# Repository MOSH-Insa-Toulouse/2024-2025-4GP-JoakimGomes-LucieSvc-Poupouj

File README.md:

<!DOCTYPE html>
<html lang="fr">
<head>
  <meta charset="UTF-8">
</head>

<body>

# 2024-2025-4GP-JoakimGomes-LucieSvc-Poupouj
## Développement d'un capteur low-tech à base de Graphite : de la conception au test

### Sommaire
<hr/>
<ul>
<li> <a href="#Introduction">Introduction </a></li>
<li> <a href="#Livrables">Livrables </a></li>
<li> <a href="#Matériel à disposition">Matériel à disposition </a></li>
<li> <a href="#Simulation électronique sur LTSpice">Simulation électronique sur LTSpice </a></li>
<li> <a href="#Design du PCB avec KiCad">Design du PCB avec KiCad </a></li>
<li> <a href="#Réalisation du Shield">Réalisation du Shield </a></li>
<li> <a href="#Développement du code Arduino">Développement du code Arduino </a></li>
<li> <a href="#Développement de l'application mobile APK avec MIT App Inventor">Développement de l'application mobile APK avec MIT App Inventor </a></li>
<li> <a href="#Banc de test">Banc de test </a></li>
<li> <a href="#Datasheet">Datasheet </a></li>
<li> <a href="#Conclusion">Conclusion </a></li>
<li> <a href="#Contact">Contact </a></li>
</ul>

<h2 id="Introduction">Introduction</h2>

<p>L'UF "du capteur au banc de test" a pour objectif de concevoir un capteur low-tech et de pouvoir ensuite le tester afin de le comparer avec un capteur commercial. Le capteur est à base de graphite, que l'on retrouve notamment dans nos crayons à papier. Son développement est issu de l'article scientifique <i>"Pencil Drawn Strain Gauges and Chemiresistors on Paper"</i>(Cheng-Wei Lin*, Zhibo Zhao*, Jaemyung Kim & Jiaxing Huang). Concevoir ce capteur est relativement simple : on applique à l'aide d'un crayon, du graphite sur un morceau de papier. Les couches de graphite déposées sur le papier agissent comme un conducteur électrique qui, lorsqu'on déforme le papier, a une conductivité (et donc une résistance) qui varie. Cela s'explique par le fait que  le nombre de chaînes de particules de graphite connectées varie selon le type de déformation. En tension, il y a moins de chaines et ces dernières sont plus courtes. C'est le contraire en compression avec des chaines plus proches, laissant ainsi mieux passer le courant.</p>

<i>Figure 1 : Image issue de l'article "Pencil Drawn Strain Gauges and Chemiresistors on Paper" qui explique les déformations des chaines sous compression et tension</i>

<h2 id="Livrables">Livrables</h2>
<p>Les livrables de ce projet sont les suivants:</p>
<ul>
<li>Un schield PCB connecté à une carte Arduino UNO et contenant divers éléments:
<ul>
<li>Notre capteur de contrainte Low-tech</li>
<li>Un capteur de flexion commercial</li>
<li>Un amplificateur dont on pourra modifier le gain grâce à un potentiomètre pour le traitement du signal</li>
<li>Un écran OLED pour afficher les données du capteur</li>
<li>Un module Bluetooth permettant la communication avec un téléphone portable</li>
<li>Un encodeur rotatoire pour naviguer dans le menu de l'écran OLED</li>

</ul>
</li></br>
<li>
Le code Arduino qui permet de faire fonctionner tout le système : la communication Bluetooth, la gestion de l'écran OLED avec affichage des données, l'utilisation des deux capteurs de contrainte, la navigation dans le menu de l'écran OLED grâce à l'encodeur rotatoire, la modification du gain grâce au potentiomètre digital.
</li></br>
<li>
L'application Android developpée sur MIT App Inventor, permettant de visualiser les données directement sur son téléphone grâce à la communication Bluetooth.
</li></br>
<li>
Une datasheet pour le capteur en graphite détaillant ses performances et caractéristiques techniques.
</li></br>
</ul>

<h2 id="Matériel à disposition">Matériel à disposition</h2>
<p>Voici la liste du matériel nécessaire pour concevoir le système ci-dessus:</p>
<ul>
<li>Résistances: une résistance de 1kΩ, une résistance de 10kΩ, deux résistances de 100 kΩ, une résistance de 47kΩ pour le Flex sensor commercial et enfin un potentiomètre digital MCP41050</li>
<li>Capacités: trois capacités de 100 nF et une capacité de 1 µF</li>
<li>Un Arduino Uno</li>
<li>Un capteur graphite fait à partir d'un support papier et d'un crayon</li>
<li>Un Flex Sensor commercial</li>
<li>Un encodeur rotatoire Keyes KY-040</li>
<li>Un écran OLED 128x64</li>
<li>Un module Bluetooth HC-05</li>
<li>Un amplificateur opérationnel LTC1050</li>
</ul>

<h2 id="Simulation électronique sur LTSpice">Simulation électronique sur LTSpice</h2>
<p>Les valeurs de résistance de notre capteur graphite sont très élevées, de l'odre du MΩ. Afin de pouvoir les mesurer correctement, il est nécessaire d’amplifier le signal avant acquisition. Le courant mesuré après application d'une tension de 5V est donc très faible. Il est donc nécessaire d'amplifier le signal avant son acquisition</p>
<p>Nous avons donc simulé un montage amplificateur transimpédance sur LTspice pour l'optimiser au mieux pour notre capteur : </p>

<i>Figure 3 : Schéma de notre montage amplificateur sur LTSpice</i>
<p>Ce montage permet d'amplifier le signal du capteur à l'aide de l'amplificateur LTC1050, puis de le filtrer. Ce dernier est divisé en 3 pour limiter le bruit  :</p>
<ul>
<li> R5 et C1 : possède une fréquence de coupure de 16Hz et permet d'atténuer les bruits présents sur le signal d’entrée</li>
<li> R3 et C4 en association avec l’AOP : filtre passe-bas avec une fréquence de coupure de 1,6 Hz, qui permet de filtrer le 50 Hz du réseau électrique</li>
<li> R4 et C2 : possède une fréquence de coupure de 1,6 kHz et permet de filtrer les bruits parasites engendrés par le traitement du signal</li>
</ul>
<p>La tension mesurée, V_ADC, permet ainsi de remonter à la valeur de résistance du graphite mesurée par le capteur, R_capteur , grâce à la formule : </p>
<p>R_capteur=R1*(1+R3/R_pot)*Vcc/V_ADC-R1-R5</p>

<h2 id="Design du PCB avec KiCad">Design du PCB avec KiCad</h2>
<p>La conception du PCB s'est faite à partir du logiciel KiCad 9.0</p>
<p>Nous avons dans un premier temps reproduit le schéma électrique du système sur l'éditeur de Schématique. Il a fallu créer certains composants et récupérer d'autres dans les librairies de symboles (résistances et capacités notamment). Nous avons associé à chaque composant une empreinte et un modèle 3D. On peut alors effectuer l'ensemble des connexions entre les composants et l'Arduino via l'éditeur de Schématique.</p>

<i>Figure 4 : ensemble du fichier Schématique sous KiCad 9.0</i>

<p>Une fois le schéma électrique terminé, il faut placer les composants sur le PCB grâce à l'éditeur de PCB. L'objectif est de placer les composants judicieusement pour respecter les contraintes imposées, notamment éviter les vias, vérifier que les composants ne se superposent pas physiquement, respecter les dimensions des pistes et l'isolation.</p>

<i>Figure 5 : Disposition des composants sur l'éditeur de PCB</i>

<p>Et voici la visualisation 3D de notre PCB avec tous les composants (l'amplificateur est sous l'écran OLED).</p>

</br>
<i>Figure 6 : Visualisation 3D du PCB et composants</i>

<h2 id="Réalisation du Shield">Réalisation du Shield</h2>
<p>Une fois la conception du PCB sur KiCad terminée, nous avons pu passer à la réalisation physique de ce PCB. 
La première étape essentielle a consisté en la vérification du schéma du circuit imprimé (PCB) à l’aide du logiciel KiCad, afin de s’assurer de sa conformité avant toute fabrication. Une fois cette vérification effectuée, le masque de gravure du PCB a été généré à partir du même logiciel.
Ensuite, a fabrication a débuté par l’insolation UV d’une plaque d’époxy recouverte d’une fine couche de cuivre et d’un film photosensible. Cette exposition à la lumière permet de durcir les zones du film correspondant aux futures pistes du circuit. La plaque a ensuite été plongée dans un révélateur, ce qui a permis de dissoudre la résine restée non exposée à la lumière. La gravure des pistes a ensuite été réalisée par immersion de la plaque dans une solution de perchlorure de fer, qui attaque le cuivre non protégé par la résine insolée. Enfin, un nettoyage à l’acétone a permis de retirer les résidus de résine, révélant ainsi les pistes de cuivre définitives du circuit imprimé.
L’ensemble de ces étapes de fabrication a été réalisé par Cathy Crouzet.

Maintenant que toutes ces étapes ont été effectué, nous allons procéder au montage du capteur. Dans un premier temps, nous avons percé tous les trous afin de pouvoir souder tous les supports des composants sur la PCB. Ensuite, nous pouvons donc souder tous les supports des composants sur la PCB (cf Figure 7). Pour finir, il suffit de simplement mettre les composants sur leur support. Notre capteur est enfin prêt à être utilisé ! (cf Figure 8) </p>

</br>
<i>Figure  7: Visualisation de la face arrière de la PCB, c'est à dire les soudures.</i>

</br>
<i>Figure  8: Visualisation de la face avant de la PCB, c'est à dire les composants</i>

<h2 id="Développement du code Arduino">Développement du code Arduino</h2>
<p>Une fois la réalisation physique de notre plaque PCB effectuée, il faut à présent développer le code Arduino. Vous pouvez voir notre code sur le github dans la partie "Code Arduino" : https://github.com/MOSH-Insa-Toulouse/2024-2025-4GP-JoakimGomes-LucieSvc-Poupouj/blob/main/Code_Arduino/Capteur_graphite.ino</p>

<h2 id="Développement de l'application mobile APK avec MIT App Inventor">Développement de l'application mobile APK avec MIT App Inventor</h2>
<p>En même temps que la réalisation du code arduino, nous avons développé une application mobile APK avec MIT App Inventor. Cette application permet d'effectuer les mesures du capteur graphite, notamment obtenir un graphe  de la résistance en fonction de la tension/compression en temps réel. L'application connecte donc via le module bluetooth notre capteur avec un téléphone android.</p>

</br>
<i>Figure  9: Visualisation du code de l'application</i>

</br>
<i>Figure  10: Visualisation de l'interface de l'application</i>

<h2 id="Banc de test">Banc de test</h2>
<p>Maintenant que notre plaque PCB est réalisé virtuellement, puis physiquement, et que notre code arduino ainsi que notre application fonctionnent correctement, nous pouvons réaliser le banc de test. L'objectif est de calculer la valeur de la résistance du capteur graphite pour différentes valeurs de déformation. Pour cela nous avons utilisé un support avec des cylindres de rayons différents (1,5 cm, 2 cm, ..., 4cm). </p>
<p>Notre papier de test ayant une épaisseur e = 0,214mm nous pouvons calculer la déformation engendrée par chacun des rayons de courbure avec la formule : ϵ = e/2r</p>
<p>Nous avons donc effectué des mesures en Tension et en Compression pour des crayons de duretés différentes (2H, B, 3B, 6B) avec une valeur de potentiomètre 1 960 Ω.</p>
<p>En traçant la courbe ΔR/R0 en fonction de la déformation, la théorie nous dit que nous devons avoir une relation linéaire entre les 2. Nous avons donc tracé une droite de régression linéaire passant par 0 pour chacune des courbes et trouvons les résultats suivants :</p>

</br>
<i>Figure  11: Courbes de ΔR/R0 en fonction de la déformation en Tension</i>

</br>
<i>Figure  12: Courbes de ΔR/R0 en fonction de la déformation en Compression</i>

<p>Comme prédit par la théorie, nous pourvons observer que en Tension la résistance augmente avec la déformation, alors qu'en Compression elle diminue. De plus, plus le crayon est sec (ex : 2H) plus la pente est élevée. Nous remarquons cependant que pour le crayons 2H semble perdre en précision quand la déformation est élevée (pente de la courbe diminue). Cela peut s'expliquer car il y a très peu de chaines de particules permettant la déformation.</p>

<h2 id="Datasheet">Datasheet</h2>
<p>Le contenu de notre Datasheet se trouve avec le lien suivant : https://github.com/MOSH-Insa-Toulouse/2024-2025-4GP-JoakimGomes-LucieSvc-Poupouj/blob/main/Datasheet_Capteur_Graphite.docx</p>

<h2 id="Conclusion">Conclusion</h2>
<p>Pour conclure, ce projet capteur a été très enrichissant sur plusieurs aspect. Nous avons pu développer de nombreuses compétences, surtout sur un aspect technique. Le plus passionant au sein de ce projet étant la réalisation du projet de A à Z. En effet, nous avons commencé par la théorie, puis la pratique avec la fabrication du capteur, jusqu'au résultat final et une analyse de mesure. C'est donc un projet très complet d'un point de vue pédagogique. 

En ce qui concerne le capteur graphite réalisé, il fonctionne et est utilisable. En revanche, il manque encore grandement de précision. En effet, il n'est pas assez "stable" et "constant" lors de son utilisation. Par exemple, il ne donne pas exactement les mêmes résultats après chaque mesure réalisée de manière identique. Ceci est sûrement dû au manque de matériel de mesure précis. Effectivement, faire les mesures "à la main" n'est pas très bon d'un point de vue rigueur et scientifique. Le capteur manque parfois de graphite ou alors la flexion ou compression n'est pas exactement bien réalisée... De plus on peut voir la limite d'utilisation au crayon 2H (cf datasheet), en dessous duquel (donc crayon moins gras), il n'est plus possible d'être mesuré. Il ne peut donc pas encore être industrialisable. Cependant, nous pouvons quand même noté que le 2H fonctionne contrairement aux études menées dans "Pencil Drawn Strain Gauges and Chemiresistors on Paper"(Cheng-Wei Lin*, Zhibo Zhao*, Jaemyung Kim & Jiaxing Huang). Nous observons notamment une bonne réponse linéaire jusqu'à une déformation de 0.007 en tension.</p>

<h2 id="Contact">Contact</h2>
<p>Pour tout besoin d'informations complémentaires, veuillez nous contacter via les adresses mails INSA suivantes :</p>
<ul>
<li>Joakim GOMES CORREIA : gomescor@insa-toulouse.fr</li>
<li>Lucie SAUVIAC : sauviac@insa-toulouse.fr</li>
<li>Nicolas POUJOL : npoujol@insa-toulouse.fr</li>
</ul>

</body>
</html>

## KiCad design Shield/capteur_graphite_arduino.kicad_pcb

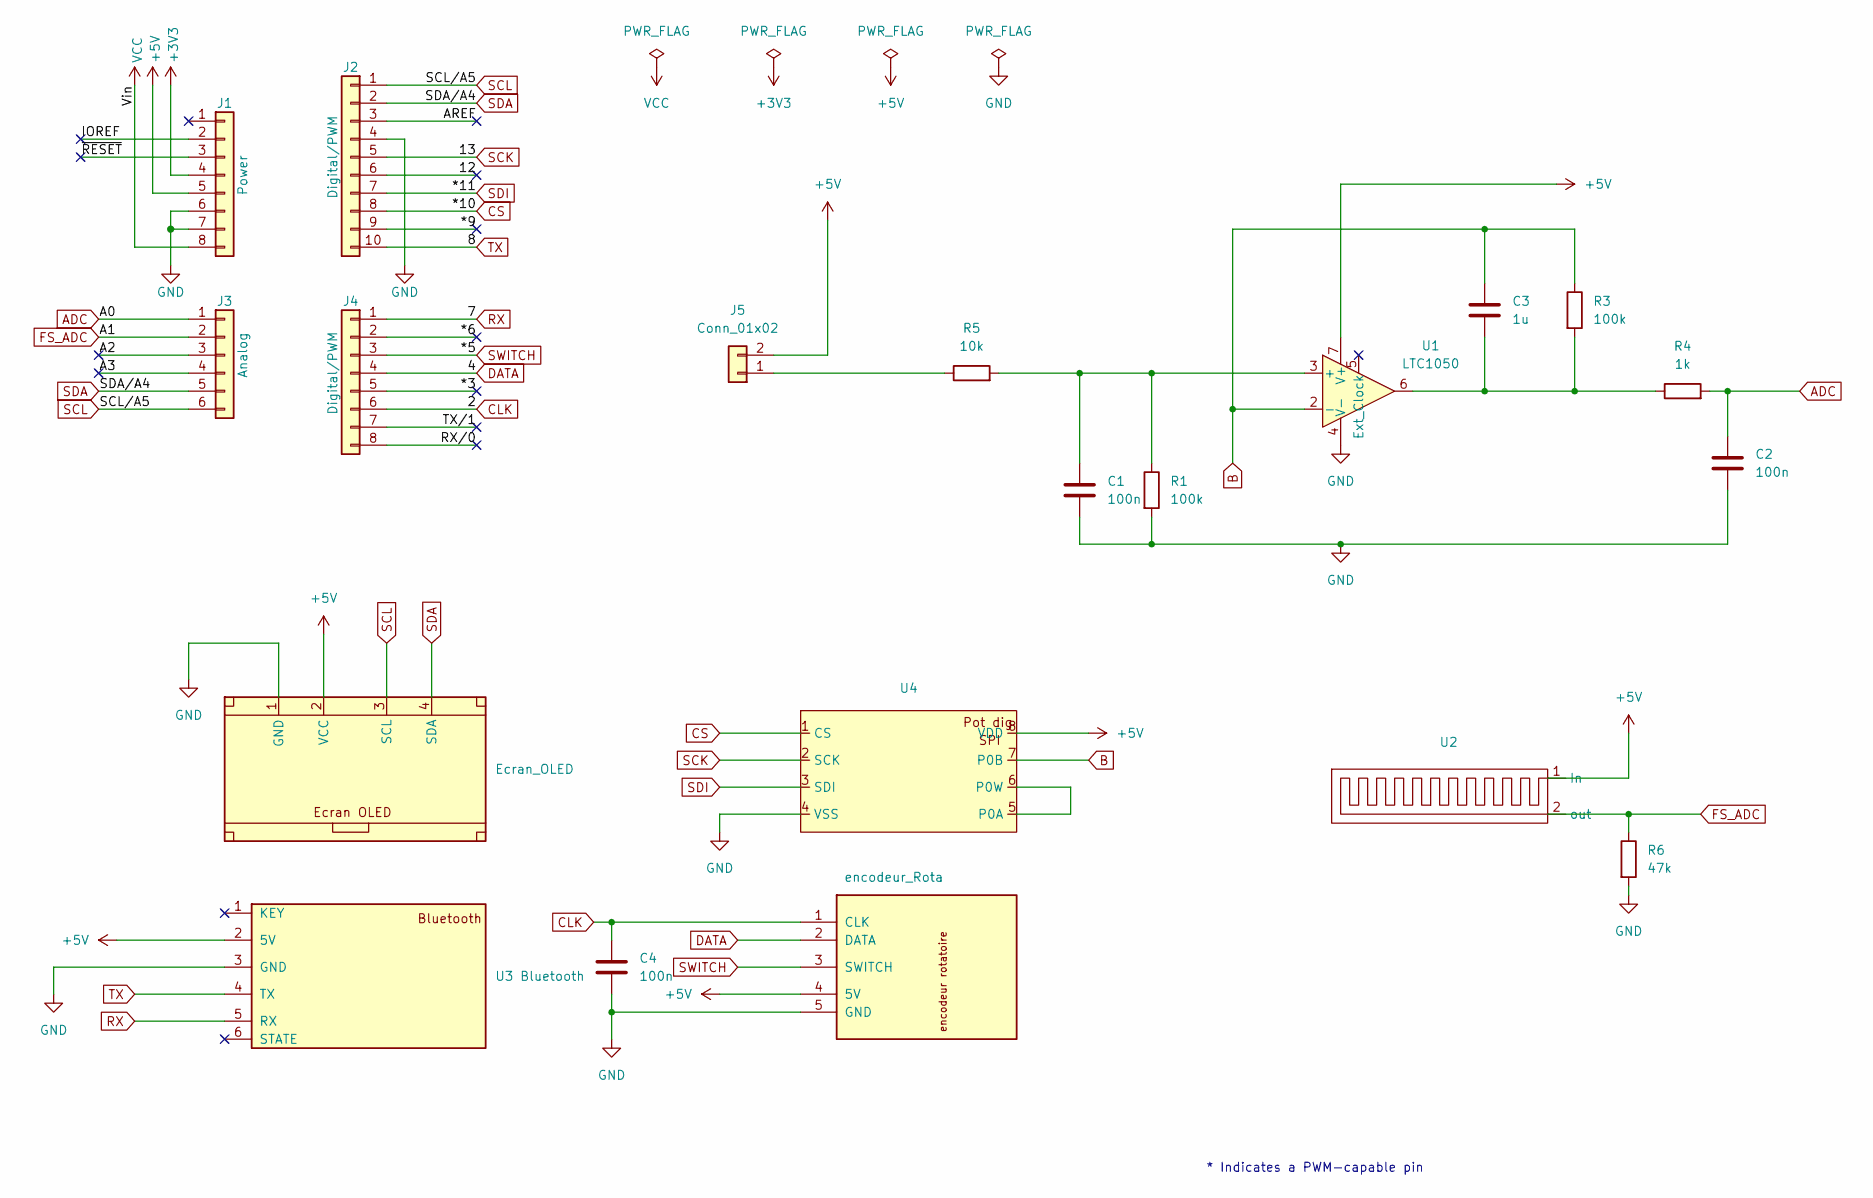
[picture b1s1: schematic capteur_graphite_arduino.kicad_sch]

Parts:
C1, C2, C4: 100n; C_Disc_D4.3mm_W1.9mm_P5.00mm
C3: 1u; C_Rect_L9.0mm_W3.9mm_P7.50mm_MKT
DS2: Ecran_OLED; OLED
J1: Power; PinSocket_1x08_P2.54mm_Vertical
J2: Digital/PWM; PinSocket_1x10_P2.54mm_Vertical
J3: Analog; PinSocket_1x06_P2.54mm_Vertical
J4: Digital/PWM; PinSocket_1x08_P2.54mm_Vertical
J5: Conn_01x02; PinSocket_1x02_P2.54mm_Vertical
R1, R3: 100k; R_Axial_DIN0207_L6.3mm_D2.5mm_P10.16mm_Horizontal
R4: 1k; R_Axial_DIN0207_L6.3mm_D2.5mm_P10.16mm_Horizontal
R5: 10k; R_Axial_DIN0207_L6.3mm_D2.5mm_P10.16mm_Horizontal
R6: 47k; R_Axial_DIN0207_L6.3mm_D2.5mm_P10.16mm_Horizontal
U1: LTC1050; DIP-8_W7.62mm
U2: flex_sensor
U3: encodeur_Rota; rotencodeur
U4: pot_dig
U5: U3 Bluetooth; Bluetooth

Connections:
+3V3: J1.4
+5V: DS2.2 (VCC), J1.5, J5.2, U1.7 (V+), U2.1 (In), U3.4 (5V), U4.8 (VDD), U5.2 (5V)
/12: J2.6
/*3: J4.5
/*6: J4.2
/*9: J2.9
/A2: J3.3
/A3: J3.4
/AREF: J2.3
/IOREF: J1.2
/RX/0: J4.8
/TX/1: J4.7
/~RESET: J1.3
ADC: C2.1, J3.1, R4.2
B: C3.1, R3.1, U1.2 (-), U4.7 (P0B)
CLK: C4.1, J4.6, U3.1 (CLK)
CS: J2.8, U4.1 (CS)
DATA: J4.4, U3.2 (DATA)
FS_ADC: J3.2, R6.1, U2.2 (out)
GND: C1.2, C2.2, C4.2, DS2.1 (GND), J1.6, J1.7, J2.4, R1.2, R6.2, U1.4 (V-), U3.5 (GND), U4.4 (VSS), U5.3 (GND)
unnamed: C3.2, R3.2, R4.1, U1.6
unnamed: J5.1, R5.1
unnamed: C1.1, R1.1, R5.2, U1.3 (+)
unnamed: U4.5 (P0A), U4.6 (P0W)
RX: J4.1, U5.5 (RX)
SCK: J2.5, U4.2 (SCK)
SCL: DS2.3 (SCL), J2.1, J3.6
SDA: DS2.4 (SDA), J2.2, J3.5
SDI: J2.7, U4.3 (SDI)
SWITCH: J4.3, U3.3 (SWITCH)
TX: J2.10, U5.4 (TX)
VCC: J1.8

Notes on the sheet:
* Indicates a PWM-capable pin

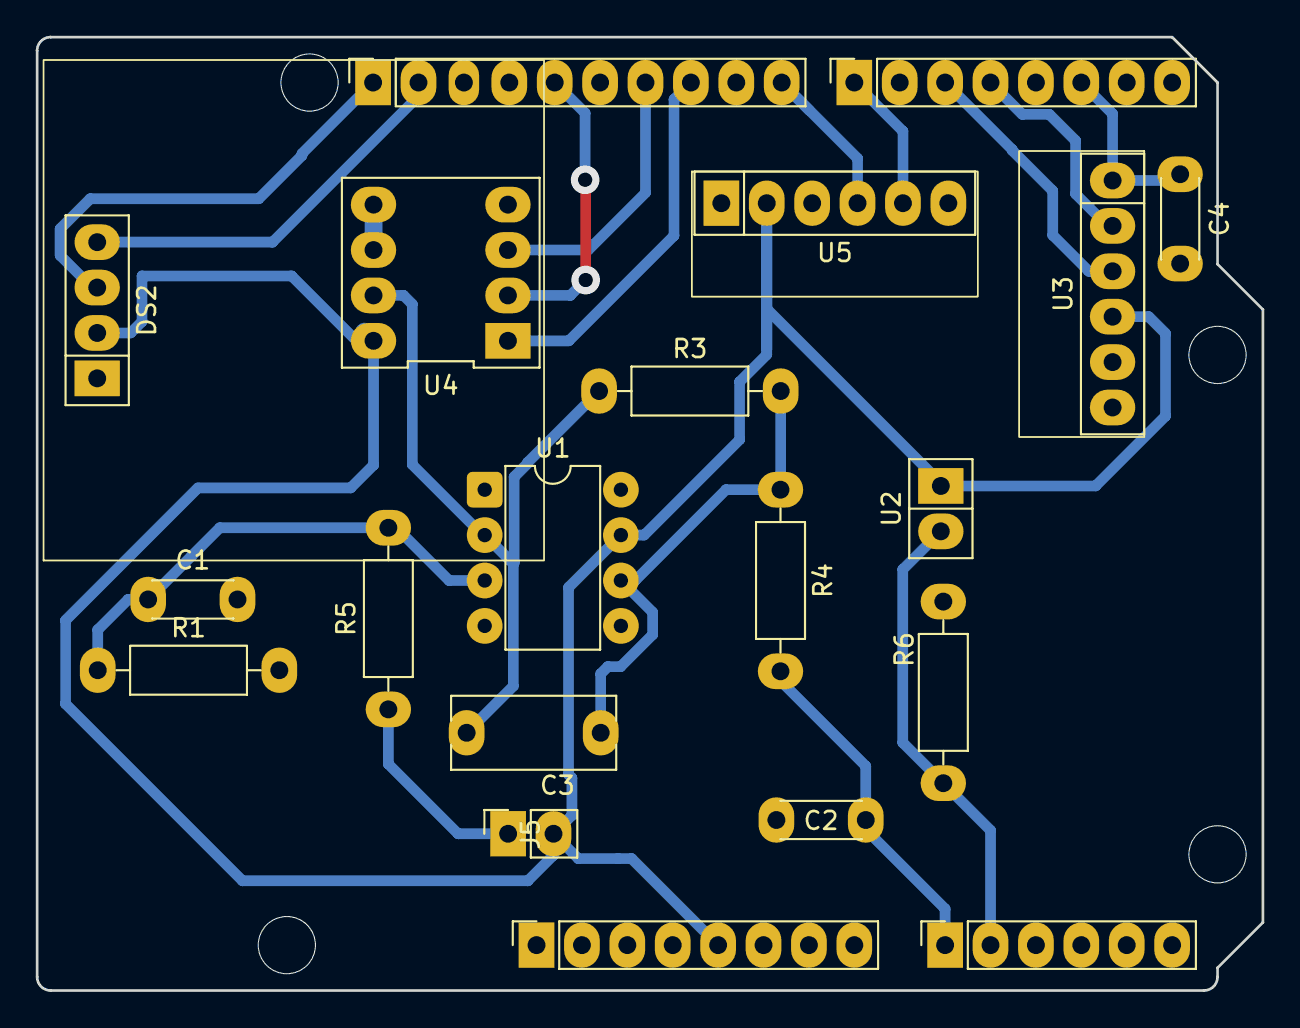
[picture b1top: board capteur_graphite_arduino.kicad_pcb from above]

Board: 2 copper layers, 68.6 x 53.3 mm, 24 parts (0 on the bottom side), 19 nets.

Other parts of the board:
MH1, MH2, MH3, MH4: MountingHole_3.2mm

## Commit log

2025-03-27 commit1
2025-03-27 change
2025-03-27 new_dossier
2025-03-27 newtext
2025-03-27 new files
2025-03-28 arduino
2025-03-29 codes_TPS
2025-03-29 codes_TP_mais_à_revoir
2025-03-31 R_flex_sensor
2025-03-31 Appli
2025-03-31 bonnes_pin_rot
2025-04-02 code_2
2025-04-02 test
2025-04-02 Rotatoire
2025-04-02 bluetooth
2025-04-02 flex
2025-04-02 code3
2025-04-02 code2_save
2025-04-02 recup
2025-04-03 nouvelle version
2025-04-03 codejo
2025-04-03 nouvelle version 2
2025-04-03 last version
2025-04-04 bluetooth fonctionne avec rotatif
2025-04-04 aaaa
2025-04-04 pcnico
2025-04-04 jecomprendspas
2025-04-04 potentiomètredemerde
2025-04-09 09/04
2025-04-09 Mesures
2025-04-11 newwwwwwwww
2025-04-11 mesureeeeeeeeeeeeeee
2025-04-20 datasheet
2025-05-16 commite readme
2025-05-16 neww
2025-05-16 newww
2025-05-16 newwww
2025-05-16 newwwwww
2025-05-16 NEwwwwwwwwww
2025-05-17 newwwwwwwwwwwwwwwwwww
2025-05-17 newws
2025-05-17 corrections
2025-05-17 conclusion
2025-05-17 LTSpice
2025-05-17 code et datasheet
2025-05-17 petite modif LTSPIc
2025-05-17 modifs
2025-05-17 application
2025-05-17 banc de test
2025-05-18 lien code
2025-05-18 liens
2025-05-18 fautes de frappe
2025-05-20 compression
2025-05-20 last
2025-05-22 graphes
2025-05-22 graphs
2025-05-29 Sensibilité et 2H
2025-05-29 image_appli
2025-05-29 appli_annotée
2025-05-30 erreur modèle encodeur
